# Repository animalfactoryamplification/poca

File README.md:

# PocaFamily

The Poca family of open-source synthesizers are a joint effort between Animal Factory Amplification and Synthfarm run by Varun Desai. The Poca family helps to introduce soldering techniques and the joy of synthesis using a simple set of modules.
<br>
Clone this repository to get access to the Gerber, EAGLE, and laser cutting files.

## PocaSynth

Based off the Forest Mimm's Stepped Tone Generator circuit, this bastardized Atari Punk console project is the perfect little beginner's synth for any enthusiast to build.

## PocaSeek

Building off the success of the PocaSynth, the PocaSeq is its new best friend. It's a simple 5 step sequencer, built off the CD4017 decade counter and 555 timer chip the Seq adds sequencing functionality to any willing module.

## PocaFilter

Inspired from the MFOS Noise Toaster and designed but Electroidiot, the PocaFilter brings much needed low-pass filtration to tame the gnarly square waves of the PocaSynth.

## PocaLFO

The only digital entry to the Poca lineup, the PocaLFO introduces 4 digital waveforms to modulate CV destinations of its Poca counterparts. Based on an Arduino Nano, the PocaLFO aims to educate students on how to write code for microcontrollers.

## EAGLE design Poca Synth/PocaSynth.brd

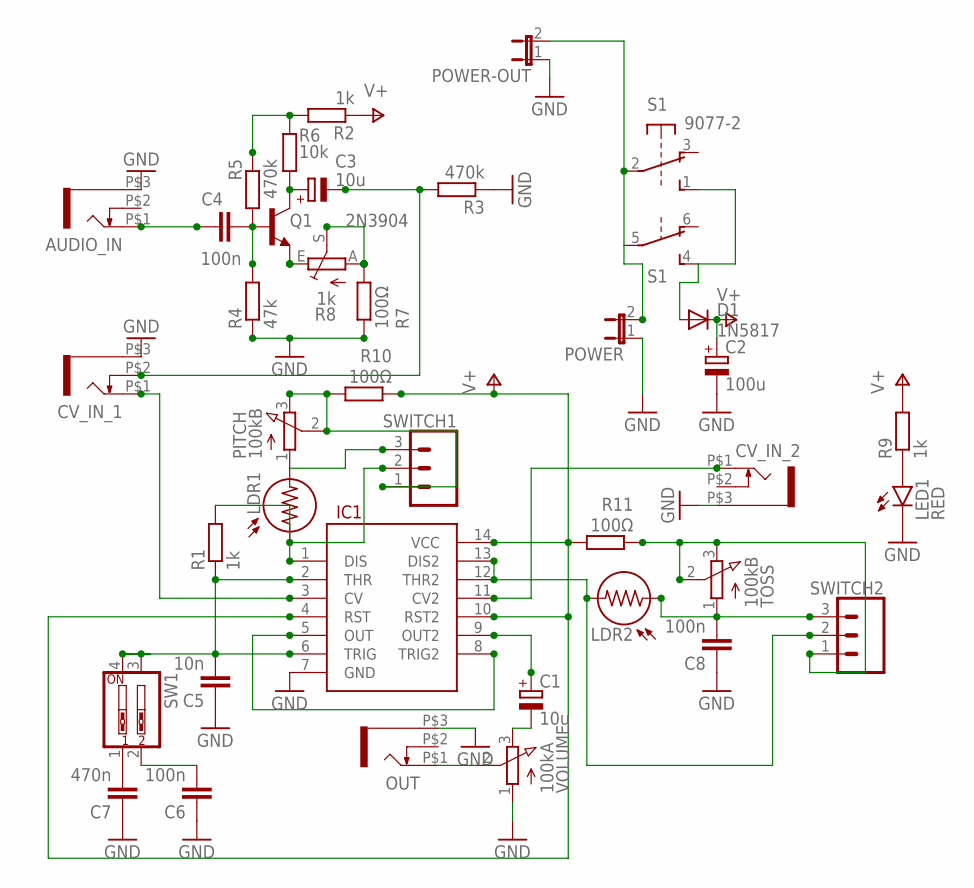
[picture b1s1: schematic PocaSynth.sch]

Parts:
AUDIO_IN: WQP-PJ301M-12_JACK
C1, C3: 10u; E2,5-7
C2: 100u; E2,5-7
C4: 100n; C050-035X075
C5: 10n; C050-030X075
C6, C8: 100n; C050-030X075
C7: 470n; C050-035X075
CV_IN_1, CV_IN_2: WQP-PJ301M-12_JACK
D1: 1N5817; DO41-10
IC1: 556; DIL14
LDR1, LDR2: LDR5MM; LDR338-54C
LED1: RED; LED3MM
OUT: WQP-PJ301M-12_JACK
PITCH: 100kB; EVUFXM
POWER: JP1E; JP1
POWER-OUT: JP1E; JP1
Q1: 2N3904; TO92-
R1, R2, R9: 1k; 0207/10
R3, R5: 470k; 0207/10
R4: 47k; 0207/10
R6: 10k; 0207/10
R7, R10, R11: 100Ω; 0207/10
R8: 1k; CA6V
S1: 9077-2
SW1: SW_DIP-2; EDG-02
SWITCH1, SWITCH2: CONN_03LOCK; 1X03_LOCK
TOSS: 100kB; EVUFXM
VOLUME: 100kA; EVUFXM

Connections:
GND: AUDIO_IN.P$3 (1), C2.-, C5.1, C6.1, C7.1, C8.1, CV_IN_1.P$3 (1), CV_IN_2.P$3 (1), IC1.7 (GND), LED1.K (C), OUT.P$3 (1), POWER.1, POWER-OUT.1, R3.1, R4.1, R7.1, VOLUME.1 (A)
unnamed: C5.2, IC1.2 (THR), IC1.6 (TRIG), R1.1, SW1.3, SW1.4
unnamed: IC1.1 (DIS), LDR1.1, R1.2, SWITCH1.2
unnamed: C6.2, SW1.2
unnamed: IC1.5 (OUT), IC1.8 (TRIG2)
unnamed: IC1.12 (THR2), IC1.13 (DIS2), LDR2.2, SWITCH2.2
unnamed: OUT.P$1 (2), VOLUME.2 (S)
unnamed: POWER.2, POWER-OUT.2, S1.2, S1.5
unnamed: CV_IN_1.P$1 (2), IC1.3 (CV)
unnamed: AUDIO_IN.P$1 (2), C4.1
unnamed: C1.+, IC1.9 (OUT2)
unnamed: C1.-, VOLUME.3 (E)
unnamed: C7.2, SW1.1
unnamed: C4.2, Q1.2 (B), R4.2, R5.1
unnamed: C3.+, Q1.1 (C), R6.1
unnamed: Q1.3 (E), R8.E
unnamed: PITCH.2 (S), PITCH.3 (E), R10.2, SWITCH1.1
unnamed: R7.2, R8.A, R8.S
unnamed: C3.-, CV_IN_1.P$2 (3), R3.2
unnamed: CV_IN_2.P$1 (2), IC1.11 (CV2)
unnamed: R11.1, SWITCH2.1, TOSS.2 (S), TOSS.3 (E)
unnamed: LDR1.2, PITCH.1 (A), SWITCH1.3
unnamed: C8.2, LDR2.1, SWITCH2.3, TOSS.1 (A)
unnamed: R2.2, R5.2, R6.2
unnamed: LED1.A, R9.1
unnamed: D1.A, S1.1 (S), S1.4 (S)
V+: C2.+, D1.C, IC1.4 (RST), IC1.10 (RST2), IC1.14 (VCC), R2.1, R9.2, R10.1, R11.2

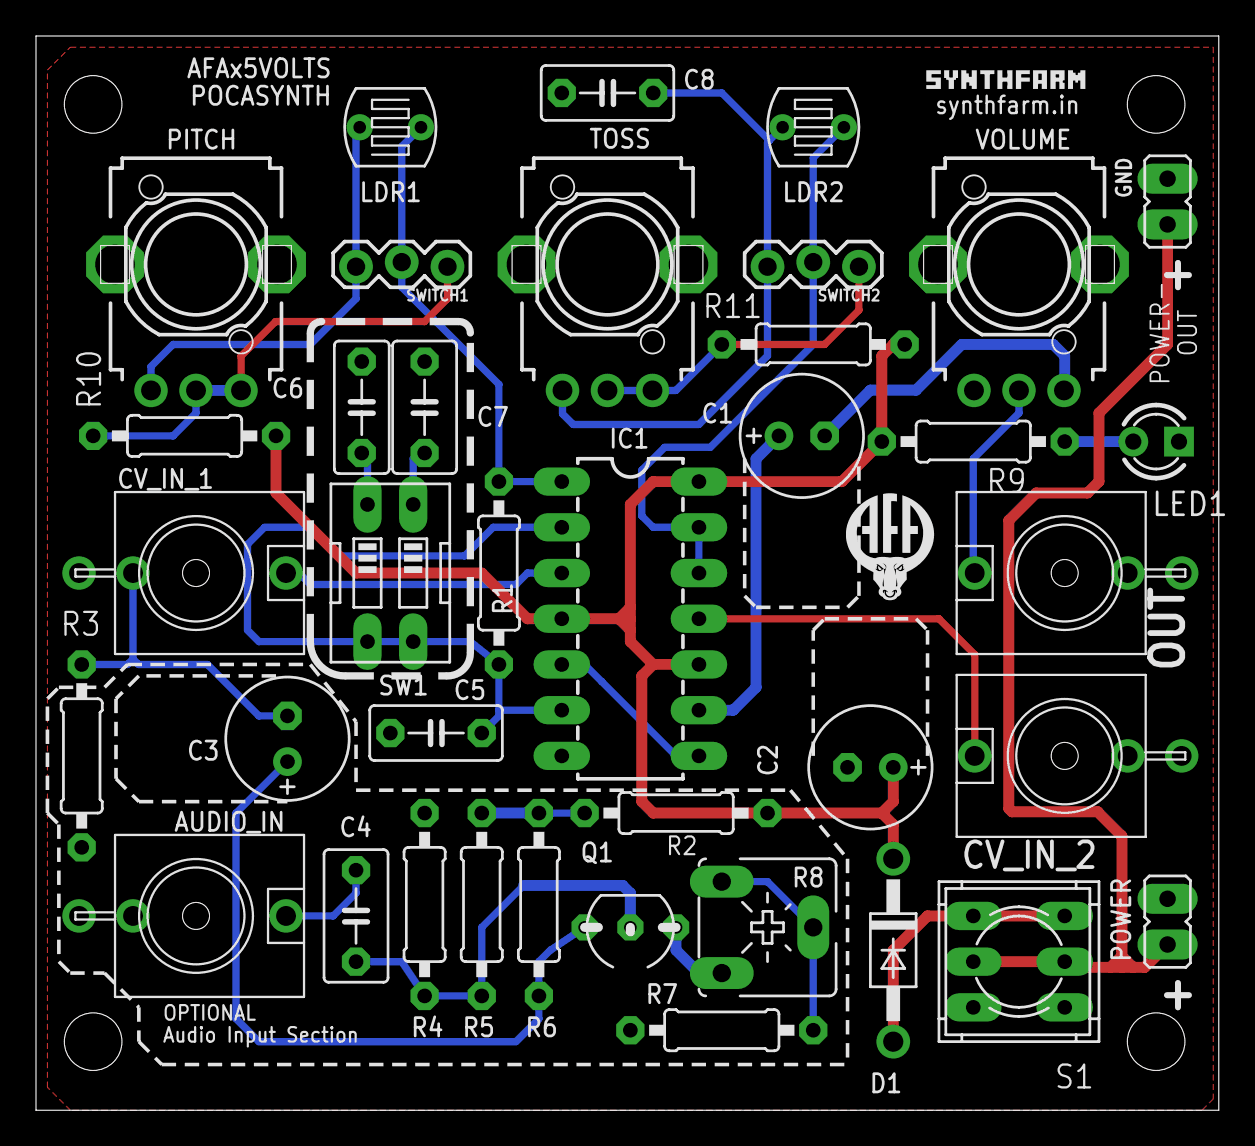
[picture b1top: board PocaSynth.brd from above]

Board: 2 copper layers, 65.7 x 59.7 mm, 38 parts (0 on the bottom side), 27 nets.

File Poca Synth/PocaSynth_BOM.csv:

"Qty";"Value";"Device";"Package";"Parts";"Description";"";
"1";"";"556";"DIL14";"IC1";"Dual timer circuit (2 555 timers in one package)";"";
"2";"";"CONN_03LOCK";"1X03_LOCK";"SWITCH1, SWITCH2";"Multi connection point. Often used as Generic Header-pin footprint for 0.1 inch spaced/style header connections";"";
"2";"";"JP1E";"JP1";"POWER, POWER-OUT";"JUMPER";"";
"2";"";"LDR5MM";"LDR338-54C";"LDR1, LDR2";"";"";
"1";"";"SW_DIP-2";"EDG-02";"SW1";"DIP SWITCH";"";
"4";"";"WQP-PJ301M-12_JACK";"WQP-PJ301M-12_JACK";"AUDIO_IN, CV_IN_1, CV_IN_2, OUT";"";"";
"1";"100kA";"EVUF3M";"EVUFXM";"VOLUME";"9 mm Square Rotary Potentiometers";"";
"2";"100kB";"EVUF3M";"EVUFXM";"PITCH, TOSS";"9 mm Square Rotary Potentiometers";"";
"2";"100n";"C-EU050-030X075";"C050-030X075";"C6, C8";"CAPACITOR, European symbol";"";
"1";"100n";"C-EU050-035X075";"C050-035X075";"C4";"CAPACITOR, European symbol";"";
"1";"100u";"CPOL-EUE2.5-7";"E2,5-7";"C2";"POLARIZED CAPACITOR, European symbol";"";
"3";"100Ω";"R-EU_0207/10";"0207/10";"R7, R10, R11";"RESISTOR, European symbol";"";
"1";"10k";"R-EU_0207/10";"0207/10";"R6";"RESISTOR, European symbol";"";
"1";"10n";"C-EU050-030X075";"C050-030X075";"C5";"CAPACITOR, European symbol";"";
"2";"10u";"CPOL-EUE2.5-7";"E2,5-7";"C1, C3";"POLARIZED CAPACITOR, European symbol";"";
"1";"1N5817";"1N4004";"DO41-10";"D1";"DIODE";"";
"3";"1k";"R-EU_0207/10";"0207/10";"R1, R2, R9";"RESISTOR, European symbol";"";
"1";"1k";"TRIM_EU-CA6V";"CA6V";"R8";"POTENTIOMETER";"";
"1";"2N3904";"2N3904";"TO92-";"Q1";"NPN Transistor";"";
"2";"470k";"R-EU_0207/10";"0207/10";"R3, R5";"RESISTOR, European symbol";"";
"1";"470n";"C-EU050-035X075";"C050-035X075";"C7";"CAPACITOR, European symbol";"";
"1";"47k";"R-EU_0207/10";"0207/10";"R4";"RESISTOR, European symbol";"";
"1";"9077-2";"9077-2";"9077-2";"S1";"MARQUARDT SWITCH 9077.0200";"";
"1";"RED";"LED3MM";"LED3MM";"LED1";"";"";

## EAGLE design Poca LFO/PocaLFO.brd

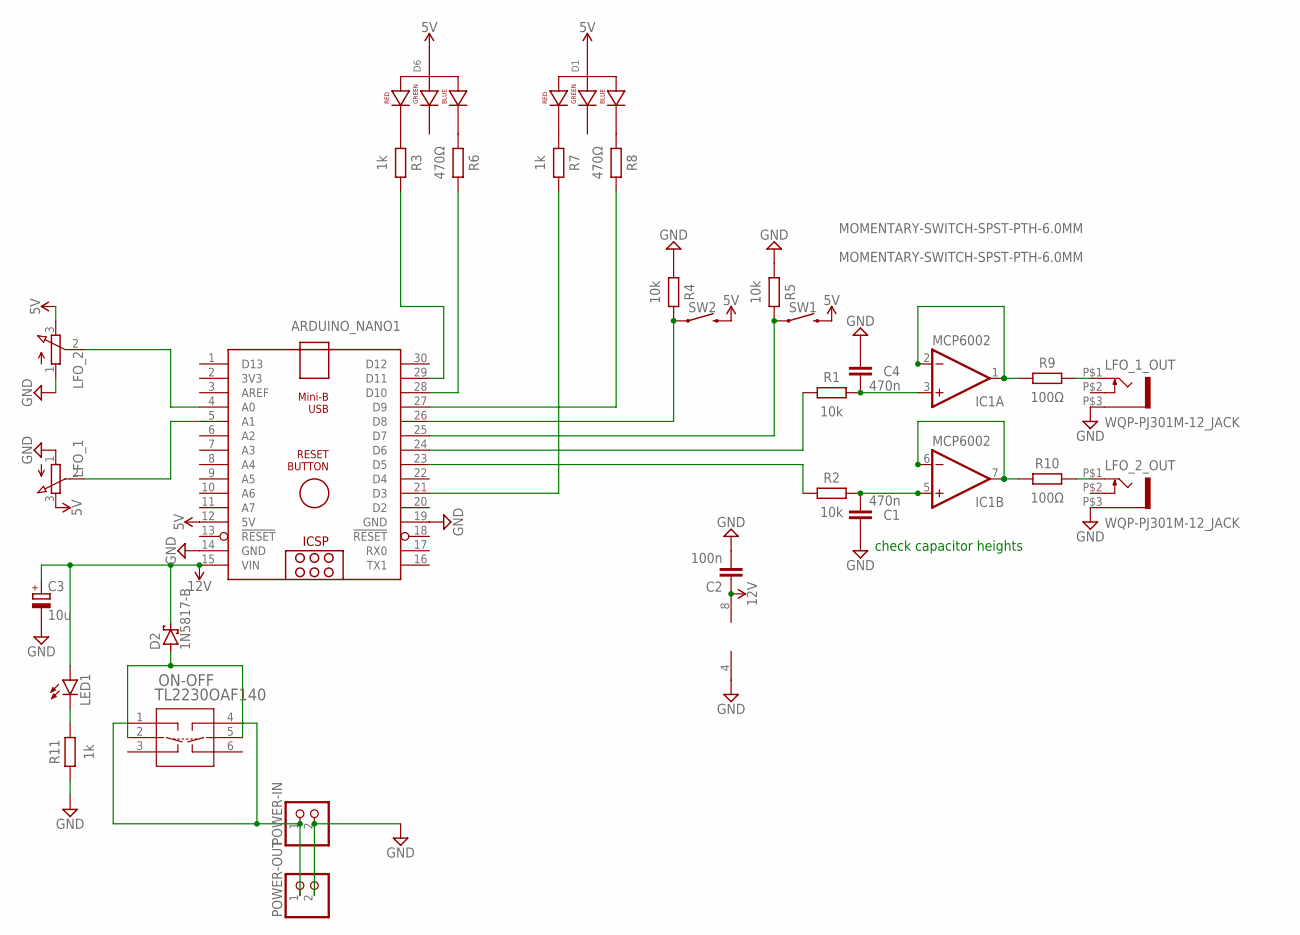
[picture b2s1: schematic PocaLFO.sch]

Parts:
ARDUINO_NANO1: ARDUINO_NANO
C1, C4: 470n; C5B3.5
C2: 100n; C2.5-4
C3: 10u; E5-5
D1, D6: LED-RGB-CA-THRUCLEAR; LED-RGB-THRU
D2: 1N5817-B; DO41-7.6
IC1: MCP6002; DIL08
LED1: LED3MM
LFO_1, LFO_2: 10kb; EVUFXM
LFO_1_OUT, LFO_2_OUT: WQP-PJ301M-12_JACK
ON-OFF: TL2230OAF140; TL2230_EWI
POWER-IN: PINHD-1X2; 1X02
POWER-OUT: PINHD-1X2; 1X02
R1, R2, R4, R5: 10k; 0207/10
R3, R7, R11: 1k; 0207/10
R6, R8: 470Ω; 0207/10
R9, R10: 100Ω; 0207/10
SW1, SW2: MOMENTARY-SWITCH-SPST-PTH-6.0MM; TACTILE_SWITCH_PTH_6.0MM

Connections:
5V: ARDUINO_NANO1.12 (5V), D1.2 (ANODE), D6.2 (ANODE), LFO_1.3 (E), LFO_2.3 (E), SW1.3 (2), SW2.3 (2)
12V: ARDUINO_NANO1.15 (VIN), C2.1, C3.+, D2.C, IC1.8 (V+), LED1.A
GND: ARDUINO_NANO1.14 (GND), ARDUINO_NANO1.19 (GND), C1.2, C2.2, C3.-, C4.1, IC1.4 (V-), LFO_1.1 (A), LFO_1_OUT.P$3 (1), LFO_2.1 (A), LFO_2_OUT.P$3 (1), POWER-IN.2, POWER-OUT.2, R4.1, R5.1, R11.1
unnamed: ARDUINO_NANO1.24 (D6), R1.1
unnamed: ARDUINO_NANO1.23 (D5), R2.1
unnamed: C4.2, IC1.3 (+IN), R1.2
unnamed: IC1.1 (OUT), IC1.2 (-IN), R9.1
unnamed: ON-OFF.1, ON-OFF.4, POWER-IN.1, POWER-OUT.1
unnamed: LFO_2_OUT.P$1 (2), R10.2
unnamed: D6.1 (RED_CATHODE), R3.1
unnamed: D6.4 (BLUE_CATHODE), R6.1
unnamed: D1.1 (RED_CATHODE), R7.1
unnamed: ARDUINO_NANO1.4 (A0), LFO_2.2 (S)
unnamed: ARDUINO_NANO1.5 (A1), LFO_1.2 (S)
unnamed: D1.4 (BLUE_CATHODE), R8.1
unnamed: ARDUINO_NANO1.29 (D11), R3.2
unnamed: ARDUINO_NANO1.26 (D8), R4.2, SW2.1
unnamed: ARDUINO_NANO1.25 (D7), R5.2, SW1.1
unnamed: ARDUINO_NANO1.28 (D10), R6.2
unnamed: ARDUINO_NANO1.21 (D3), R7.2
unnamed: ARDUINO_NANO1.27 (D9), R8.2
unnamed: C1.1, IC1.5 (+IN), R2.2
unnamed: IC1.6 (-IN), IC1.7 (OUT), R10.1
unnamed: LFO_1_OUT.P$1 (2), R9.2
unnamed: LED1.K (C), R11.2
unnamed: D2.A, ON-OFF.2, ON-OFF.5

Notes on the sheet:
check capacitor heights

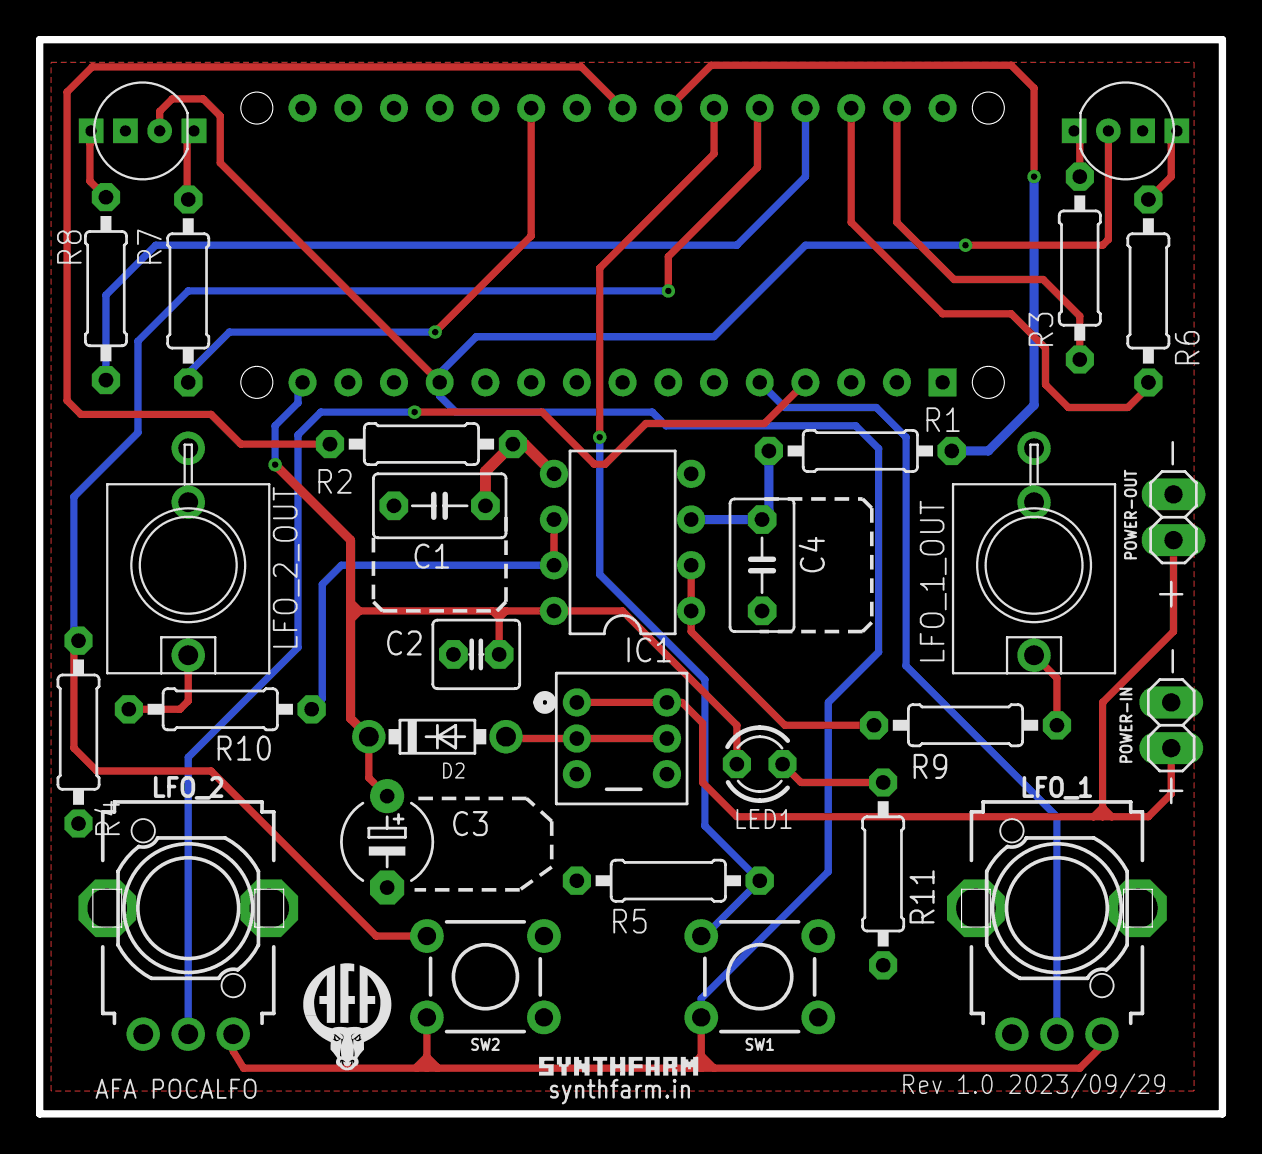
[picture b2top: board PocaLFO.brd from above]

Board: 2 copper layers, 65.7 x 59.7 mm, 30 parts (1 on the bottom side), 26 nets.

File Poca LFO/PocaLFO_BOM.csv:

"Qty";"Value";"Device";"Package";"Parts";"Description";"COPYRIGHT";"MANUFACTURER_PART_NUMBER";"MFR_NAME";"POPULARITY";"PROD_ID";"SF_SKU";"SPICEPREFIX";
"1";"";"ARDUINO_NANO";"ARDUINO_NANO";"ARDUINO_NANO1";"Arduino Nano V3.0";"";"";"";"";"";"";"";
"1";"";"LED3MM";"LED3MM";"LED1";"LED";"";"";"";"97";"";"";"";
"2";"";"PINHD-1X2";"1X02";"POWER-IN, POWER-OUT";"PIN HEADER";"";"";"";"98";"";"";"";
"1";"100n";"C2.5/4";"C2.5-4";"C2";"CAPACITOR";"";"";"";"6";"";"";"";
"2";"100Ω";"R-EU_0207/10";"0207/10";"R9, R10";"RESISTOR, European symbol";"";"";"";"81";"";"";"R";
"4";"10k";"R-EU_0207/10";"0207/10";"R1, R2, R4, R5";"RESISTOR, European symbol";"";"";"";"81";"";"";"R";
"2";"10kb";"EVUF3M";"EVUFXM";"LFO_1, LFO_2";"9 mm Square Rotary Potentiometers";"";"";"";"";"";"";"";
"1";"10u";"CPOL-EUE5-5";"E5-5";"C3";"POLARIZED CAPACITOR, European symbol";"";"";"";"6";"";"";"C";
"1";"1N5817-B";"1N5817-B";"DO41-7.6";"D2";"1.0A SCHOTTKY BARRIER RECTIFIER";"";"";"";"0";"";"";"";
"3";"1k";"R-EU_0207/10";"0207/10";"R3, R7, R11";"RESISTOR, European symbol";"";"";"";"81";"";"";"R";
"2";"470n";"C5/3.5";"C5B3.5";"C1, C4";"CAPACITOR";"";"";"";"3";"";"";"";
"2";"470Ω";"R-EU_0207/10";"0207/10";"R6, R8";"RESISTOR, European symbol";"";"";"";"81";"";"";"R";
"2";"LED-RGB-CA-THRUCLEAR";"LED-RGB-CA-THRUCLEAR";"LED-RGB-THRU";"D1, D6";"RGB Through-hole common anode";"";"";"";"";"DIO-10631";"";"";
"1";"MCP6002";"TL072P";"DIL08";"IC1";"OP AMP";"";"";"";"13";"";"";"";
"2";"MOMENTARY-SWITCH-SPST-PTH-6.0MM";"MOMENTARY-SWITCH-SPST-PTH-6.0MM";"TACTILE_SWITCH_PTH_6.0MM";"SW1, SW2";"Momentary Switch (Pushbutton) - SPST";"";"";"";"";" SWCH-08441";"COM-00097";"";
"1";"TL2230OAF140";"TL2230OAF140";"TL2230_EWI";"ON-OFF";"";"Copyright (C) 2023 Ultra Librarian. All rights reserved.";"TL2230OAF140";"E-Switch";"";"";"";"";
"2";"WQP-PJ301M-12_JACK";"WQP-PJ301M-12_JACK";"WQP-PJ301M-12_JACK";"LFO_1_OUT, LFO_2_OUT";"";"";"";"";"";"";"";"";

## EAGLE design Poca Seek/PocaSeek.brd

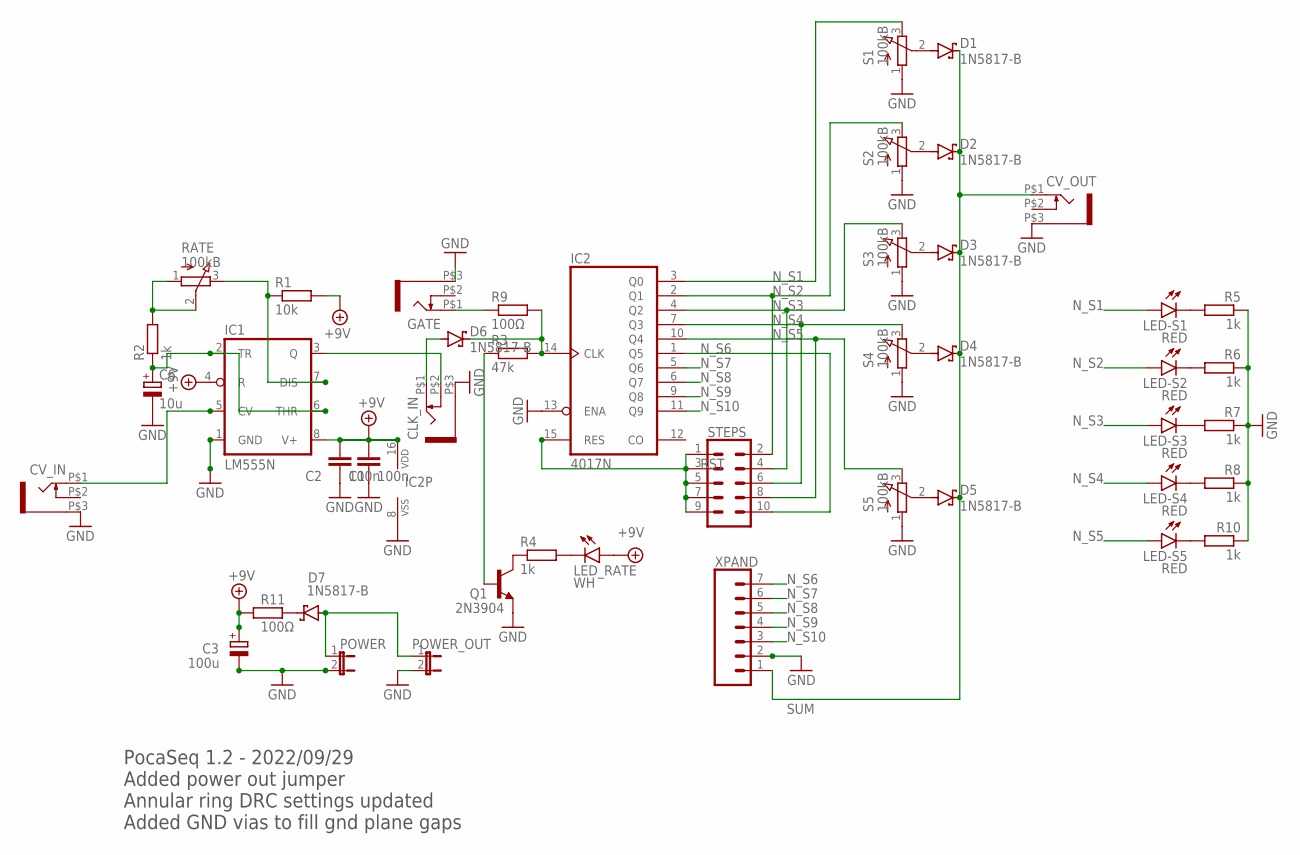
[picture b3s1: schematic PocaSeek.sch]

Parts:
C1, C2: 100n; C050-024X044
C3: 100u; E2,5-7
C6: 10u; E2,5-6
CLK_IN: WQP-PJ301M-12_JACK
CV_IN: WQP-PJ301M-12_JACK
CV_OUT: WQP-PJ301M-12_JACK
D1, D2, D3, D4, D5, D6, D7: 1N5817-B; DO41-7.6
GATE: WQP-PJ301M-12_JACK
IC1: LM555N; DIL08
IC2: 4017N; DIL16
LED-S1, LED-S2, LED-S3, LED-S4, LED-S5: RED; LED3MM
LED_RATE: WH; LED3MM
POWER: JP1E; JP1
POWER_OUT: JP1E; JP1
Q1: 2N3904; TO92
R1: 10k; 0204/7
R2, R4: 1k; 0204/7
R3: 47k; 0204/7
R5, R6, R7, R8, R10: 1k; 0204V
R9, R11: 100Ω; 0204/7
RATE: 100kB; EVUFXM
S1, S2, S3, S4, S5: 100kB; EVUFXM
STEPS: CONN_05X2PTH; 2X5
XPAND: CONN_07LOCK; 1X07_LOCK

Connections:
+9V: C1.1, C2.1, C3.+, IC1.4 (R), IC1.8 (V+), IC2.16 (VDD), LED_RATE.A, R1.2, R11.1
GND: C1.2, C2.2, C3.-, C6.-, CLK_IN.P$3 (1), CV_IN.P$3 (1), CV_OUT.P$3 (1), GATE.P$3 (1), IC1.1 (GND), IC2.8 (VSS), IC2.13 (ENA), POWER.2, POWER_OUT.2, Q1.3 (E), R5.1, R6.1, R7.1, R8.1, R10.1, S1.1 (A), S2.1 (A), S3.1 (A), S4.1 (A), S5.1 (A), XPAND.2
unnamed: D1.A, S1.2 (S)
unnamed: CLK_IN.P$2 (3), IC1.3 (Q)
unnamed: D2.A, S2.2 (S)
unnamed: D6.C, IC2.14 (CLK), R3.2, R9.2
unnamed: D5.A, S5.2 (S)
unnamed: LED-S1.K (C), R5.2
unnamed: GATE.P$1 (2), R9.1
unnamed: D3.A, S3.2 (S)
unnamed: D4.A, S4.2 (S)
unnamed: R2.2, RATE.1 (A), RATE.2 (S)
unnamed: LED-S3.K (C), R7.2
unnamed: Q1.2 (B), R3.1
unnamed: CLK_IN.P$1 (2), D6.A
unnamed: CV_IN.P$1 (2), IC1.5 (CV)
unnamed: C6.+, IC1.2 (TR), IC1.6 (THR), R2.1
unnamed: IC1.7 (DIS), R1.1, RATE.3 (E)
unnamed: LED-S4.K (C), R8.2
unnamed: Q1.1 (C), R4.1
unnamed: LED_RATE.K (C), R4.2
unnamed: LED-S5.K (C), R10.2
unnamed: LED-S2.K (C), R6.2
unnamed: D7.C, R11.2
unnamed: D7.A, POWER.1, POWER_OUT.1
N_S1: IC2.3 (Q0), LED-S1.A, S1.3 (E)
N_S2: IC2.2 (Q1), LED-S2.A, S2.3 (E), STEPS.2
N_S3: IC2.4 (Q2), LED-S3.A, S3.3 (E), STEPS.4
N_S4: IC2.7 (Q3), LED-S4.A, S4.3 (E), STEPS.6
N_S5: IC2.10 (Q4), LED-S5.A, S5.3 (E), STEPS.8
N_S6: IC2.1 (Q5), STEPS.10, XPAND.7
N_S7: IC2.5 (Q6), XPAND.6
N_S8: IC2.6 (Q7), XPAND.5
N_S9: IC2.9 (Q8), XPAND.4
N_S10: IC2.11 (Q9), XPAND.3
RST: IC2.15 (RES), STEPS.1, STEPS.3, STEPS.5, STEPS.7, STEPS.9
SUM: CV_OUT.P$1 (2), D1.C, D2.C, D3.C, D4.C, D5.C, XPAND.1

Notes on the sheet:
PocaSeq 1.2 - 2022/09/29 Added power out jumper Annular ring DRC settings updated Added GND vias to fill gnd plane gaps

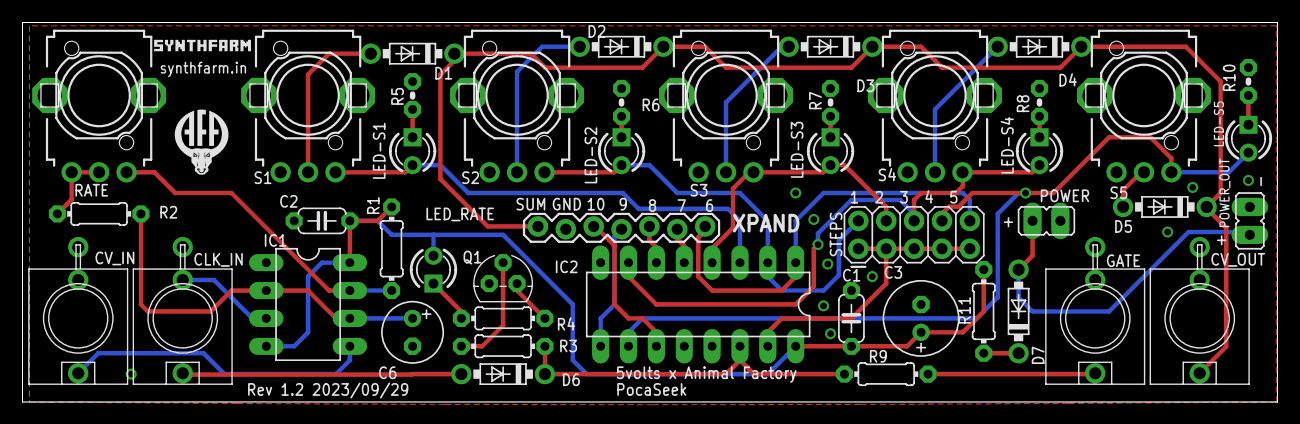
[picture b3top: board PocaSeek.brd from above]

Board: 2 copper layers, 114.4 x 34.6 mm, 45 parts (0 on the bottom side), 37 nets.

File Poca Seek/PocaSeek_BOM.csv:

"Qty";"Value";"Device";"Package";"Parts";"Description";"POPULARITY";"PROD_ID";"SF_ID";
"1";"";"CONN_05X2PTH";"2X5";"STEPS";"Multi connection point. Often used as Generic Header-pin footprint for 0.1 inch spaced/style header connections";"";"CONN-08499";"PRT-0778";
"1";"";"CONN_07LOCK";"1X07_LOCK";"XPAND";"Multi connection point. Often used as Generic Header-pin footprint for 0.1 inch spaced/style header connections";"";"";"";
"2";"";"JP1E";"JP1";"POWER, POWER_OUT";"JUMPER";"";"";"";
"4";"";"WQP-PJ301M-12_JACK";"WQP-PJ301M-12_JACK";"CLK_IN, CV_IN, CV_OUT, GATE";"";"";"";"";
"6";"100kB";"EVUF3M";"EVUFXM";"RATE, S1, S2, S3, S4, S5";"9 mm Square Rotary Potentiometers";"";"";"";
"2";"100n";"C-EU050-024X044";"C050-024X044";"C1, C2";"CAPACITOR, European symbol";"";"";"";
"1";"100u";"CPOL-EUE2.5-7";"E2,5-7";"C3";"POLARIZED CAPACITOR, European symbol";"";"";"";
"2";"100Ω";"R-EU_0204/7";"0204/7";"R9, R11";"RESISTOR, European symbol";"";"";"";
"1";"10k";"R-EU_0204/7";"0204/7";"R1";"RESISTOR, European symbol";"";"";"";
"1";"10u";"CPOL-EUE2.5-6";"E2,5-6";"C6";"POLARIZED CAPACITOR, European symbol";"";"";"";
"7";"1N5817-B";"1N5817-B";"DO41-7.6";"D1, D2, D3, D4, D5, D6, D7";"1.0A SCHOTTKY BARRIER RECTIFIER";"0";"";"";
"5";"1k";"R-EU_0204/2V";"0204V";"R5, R6, R7, R8, R10";"RESISTOR, European symbol";"";"";"";
"2";"1k";"R-EU_0204/7";"0204/7";"R2, R4";"RESISTOR, European symbol";"";"";"";
"1";"2N3904";"2N3904";"TO92";"Q1";"NPN TRANSISTOR";"";"";"";
"1";"4017N";"4017N";"DIL16";"IC2";"COUNTER/DIVIDER";"";"";"";
"1";"47k";"R-EU_0204/7";"0204/7";"R3";"RESISTOR, European symbol";"";"";"";
"1";"LM555N";"LM555N";"DIL08";"IC1";"TIMER";"";"";"";
"5";"RED";"LED3MM";"LED3MM";"LED-S1, LED-S2, LED-S3, LED-S4, LED-S5";"";"";"";"";
"1";"WH";"LED3MM";"LED3MM";"LED_RATE";"";"";"";"";

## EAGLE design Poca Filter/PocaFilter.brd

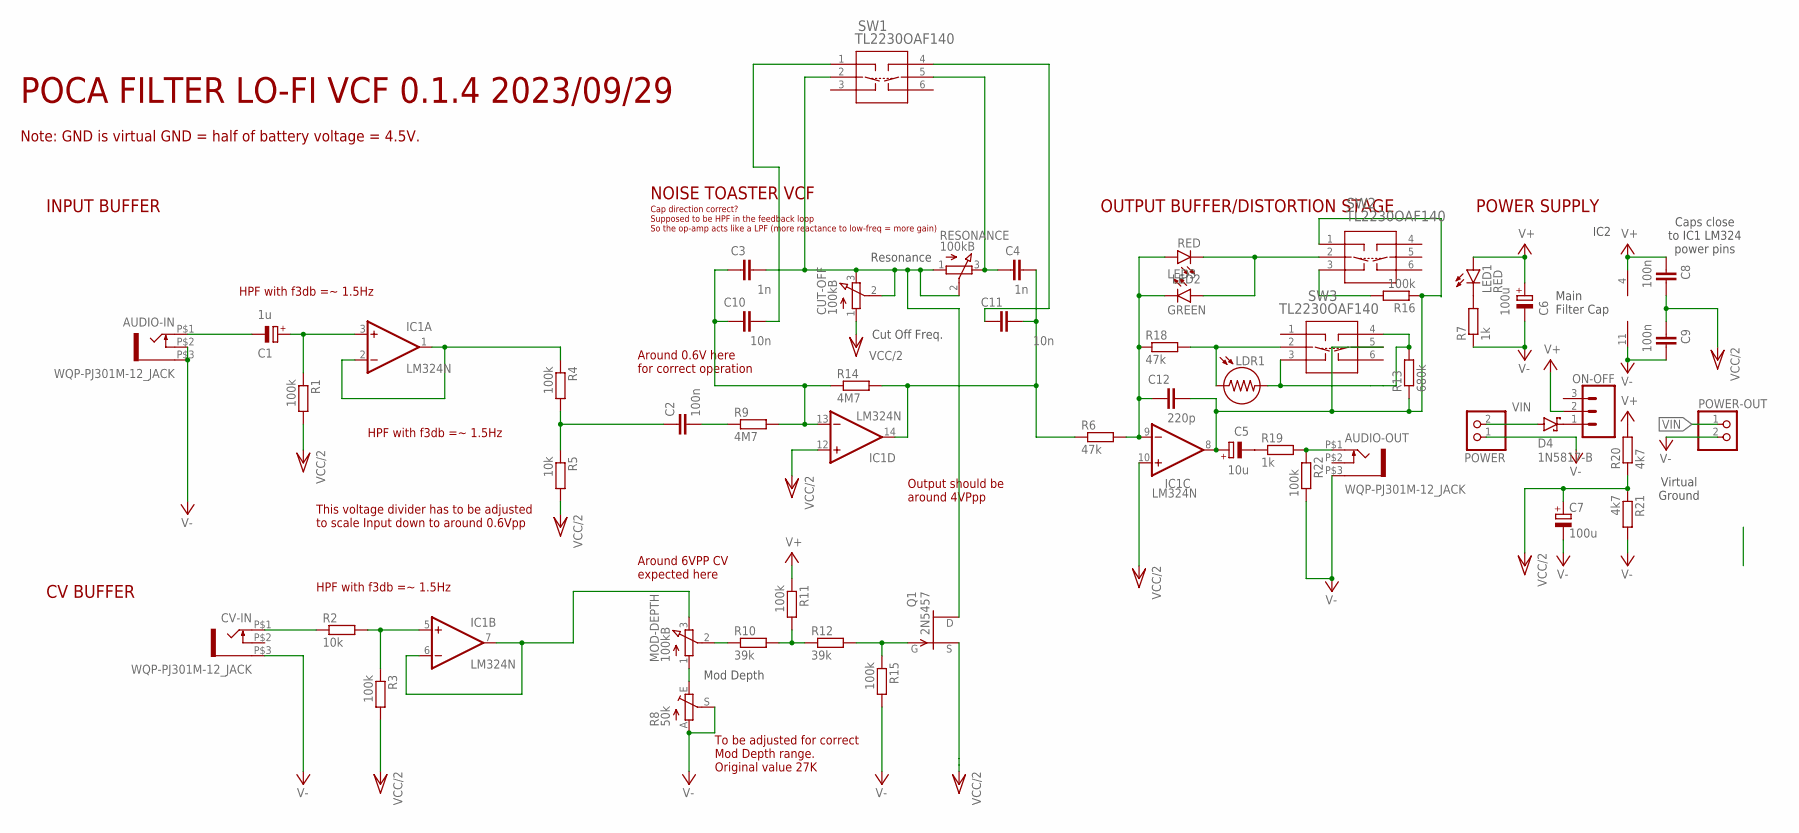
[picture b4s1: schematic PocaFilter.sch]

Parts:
AUDIO-IN: WQP-PJ301M-12_JACK
AUDIO-OUT: WQP-PJ301M-12_JACK
C1: 1u; E2,5-6
C2: 100n; C050-030X075
C3, C4: 1n; C050-030X075
C5: 10u; E2,5-6
C6: 100u; E2,5-6
C7: 100u; E2,5-6E
C8, C9: 100n; C025-025X050
C10, C11: 10n; C050-030X075
C12: 220p; C025-025X050
CUT-OFF: 100kB; EVUFXM
CV-IN: WQP-PJ301M-12_JACK
D4: 1N5817-B; DO41-7.6
IC1: LM324N; DIL14
LDR1: LDR5MM; LDR338-54C
LED1: RED; LED3MM
LED2: RED; LED_3MM
LED3: GREEN; LED_3MM
MOD-DEPTH: 100kB; EVUFXM
ON-OFF: CONN_03LOCK; 1X03_LOCK
POWER: PINHD-1X2; 1X02
POWER-OUT: PINHD-1X2; 1X02
Q1: 2N5457; TO92
R1, R3, R4, R11, R15, R22: 100k; 0207/10
R2, R5: 10k; 0207/10
R6, R18: 47k; 0207/10
R7, R19: 1k; 0207/10
R8: 50k; CA6V
R9, R14: 4M7; 0207/10
R10, R12: 39k; 0207/10
R13: 680k; 0207/10
R16: 100k; 0204/7
R20, R21: 4k7; 0207/10
RESONANCE: 100kB; EVUFXM
SW1, SW2, SW3: TL2230OAF140; TL2230_EWI

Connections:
unnamed: CV-IN.P$1 (2), R2.1
unnamed: MOD-DEPTH.1 (A), R8.E
unnamed: IC1.1 (OUT), IC1.2 (-IN), R4.1
unnamed: C1.+, IC1.3 (+IN), R1.1
unnamed: IC1.6 (-IN), IC1.7 (OUT), MOD-DEPTH.3 (E)
unnamed: AUDIO-IN.P$1 (2), C1.-
unnamed: LDR1.2, R13.2, SW3.3, SW3.4
unnamed: AUDIO-OUT.P$1 (2), R19.2, R22.1
unnamed: C5.-, R19.1
unnamed: IC1.5 (+IN), R2.2, R3.1
unnamed: C12.1, IC1.9 (-IN), LED2.A, LED3.K (C), R6.2, R18.1
unnamed: LDR1.1, R18.2, SW3.2
unnamed: LED2.K (C), LED3.A, SW2.2
unnamed: C11.1, SW1.4
unnamed: C10.2, SW1.1
unnamed: LED1.K (C), R7.2
unnamed: C5.+, C12.2, IC1.8 (OUT), R13.1, R16.1, SW2.1, SW3.5
unnamed: R16.2, SW2.3
unnamed: D4.C, ON-OFF.1
unnamed: C2.2, R9.1
unnamed: C3.1, C10.1, IC1.13 (-IN), R9.2, R14.1
unnamed: R10.2, R11.2, R12.1
unnamed: Q1.1 (G), R12.2, R15.1
V+: C6.+, C8.1, IC1.4 (V+), LED1.A, ON-OFF.2, R11.1, R20.2
V-: AUDIO-IN.P$2 (3), AUDIO-IN.P$3 (1), AUDIO-OUT.P$3 (1), C6.-, C7.-, C9.2, CV-IN.P$3 (1), IC1.11 (V-), POWER.1, POWER-OUT.2, R7.1, R8.A, R8.S, R15.2, R21.2, R22.2
VCC/2: C7.+, C8.2, C9.1, CUT-OFF.1 (A), IC1.10 (+IN), IC1.12 (+IN), Q1.2 (S), R1.2, R3.2, R5.2, R20.1, R21.1
VIN: D4.A, POWER.2, POWER-OUT.1
X8: C2.1, R4.2, R5.1
X9: C3.2, CUT-OFF.2 (S), CUT-OFF.3 (E), Q1.3 (D), RESONANCE.1 (A), RESONANCE.2 (S), SW1.2
X10: C4.1, RESONANCE.3 (E), SW1.5
X12: C4.2, C11.2, IC1.14 (OUT), R6.1, R14.2
X14: MOD-DEPTH.2 (S), R10.1

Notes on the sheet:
Mod Depth
NOISE TOASTER VCF
Cut Off Freq.
Resonance
POWER SUPPLY
IC2
Virtual Ground
Caps close to IC1 LM324 power pins
Main Filter Cap
POCA FILTER LO-FI VCF 0.1.4 2023/09/29
This voltage divider has to be adjusted to scale Input down to around 0.6Vpp
OUTPUT BUFFER/DISTORTION STAGE
INPUT BUFFER
CV BUFFER
Around 6VPP CV expected here
To be adjusted for correct Mod Depth range. Original value 27K
Note: GND is virtual GND = half of battery voltage = 4.5V.
Output should be around 4VPpp
Around 0.6V here for correct operation
HPF with f3db =~ 1.5Hz
Cap direction correct? Supposed to be HPF in the feedback loop So the op-amp acts like a LPF (more reactance to low-freq = more gain)

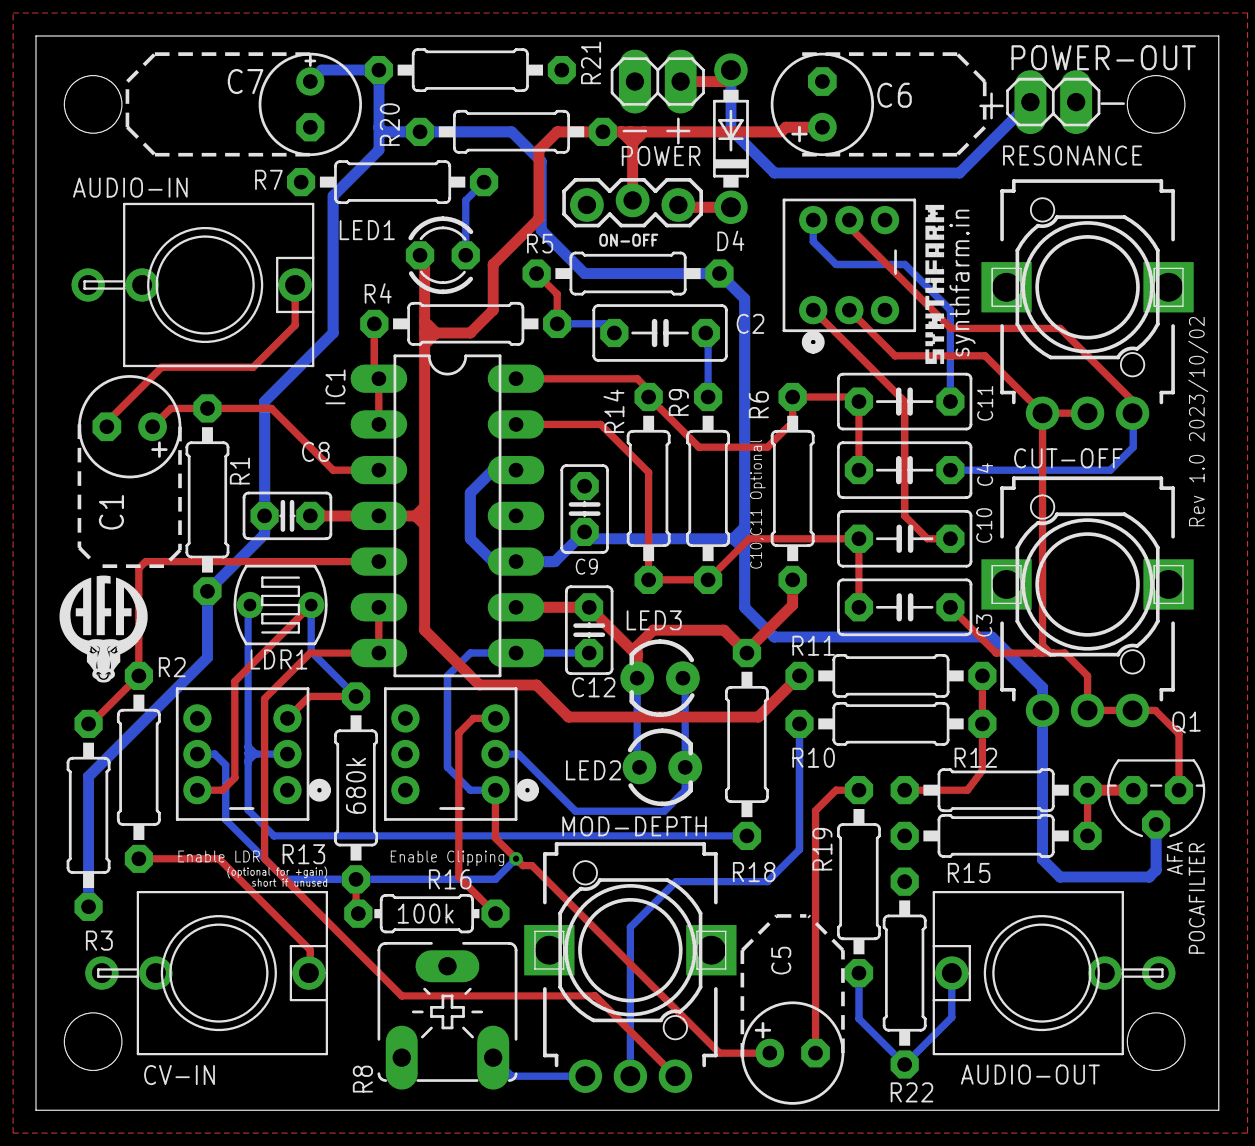
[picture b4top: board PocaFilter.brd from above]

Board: 2 copper layers, 65.7 x 59.7 mm, 52 parts (0 on the bottom side), 32 nets.

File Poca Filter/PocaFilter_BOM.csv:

"Qty";"Value";"Device";"Package";"Parts";"Description";"COPYRIGHT";"MANUFACTURER_PART_NUMBER";"MFR_NAME";"POPULARITY";"PROD_ID";"SPICEPREFIX";
"1";"";"CONN_03LOCK";"1X03_LOCK";"ON-OFF";"Multi connection point. Often used as Generic Header-pin footprint for 0.1 inch spaced/style header connections";"";"";"";"";"";"";
"1";"";"LDR5MM";"LDR338-54C";"LDR1";"";"";"";"";"";"";"";
"2";"";"PINHD-1X2";"1X02";"POWER, POWER-OUT";"PIN HEADER";"";"";"";"98";"";"";
"1";"100k";"R-EU_0204/7";"0204/7";"R16";"RESISTOR, European symbol";"";"";"";"79";"";"R";
"6";"100k";"R-EU_0207/10";"0207/10";"R1, R3, R4, R11, R15, R22";"RESISTOR, European symbol";"";"";"";"81";"";"R";
"3";"100kB";"EVUF3M";"EVUFXM";"CUT-OFF, MOD-DEPTH, RESONANCE";"9 mm Square Rotary Potentiometers";"";"";"";"0";"";"";
"2";"100n";"C-EU025-025X050";"C025-025X050";"C8, C9";"CAPACITOR, European symbol";"";"";"";"65";"";"C";
"1";"100n";"C-EU050-030X075";"C050-030X075";"C2";"CAPACITOR, European symbol";"";"";"";"9";"";"C";
"1";"100u";"CPOL-EUE2,5-6E";"E2,5-6E";"C7";"POLARIZED CAPACITOR, European symbol";"";"";"";"27";"";"C";
"1";"100u";"CPOL-EUE2.5-6";"E2,5-6";"C6";"POLARIZED CAPACITOR, European symbol";"";"";"";"26";"";"C";
"2";"10k";"R-EU_0207/10";"0207/10";"R2, R5";"RESISTOR, European symbol";"";"";"";"81";"";"R";
"2";"10n";"C-EU050-030X075";"C050-030X075";"C10, C11";"CAPACITOR, European symbol";"";"";"";"9";"";"C";
"1";"10u";"CPOL-EUE2.5-6";"E2,5-6";"C5";"POLARIZED CAPACITOR, European symbol";"";"";"";"26";"";"C";
"1";"1N5817-B";"1N5817-B";"DO41-7.6";"D4";"1.0A SCHOTTKY BARRIER RECTIFIER";"";"";"";"0";"";"";
"2";"1k";"R-EU_0207/10";"0207/10";"R7, R19";"RESISTOR, European symbol";"";"";"";"81";"";"R";
"2";"1n";"C-EU050-030X075";"C050-030X075";"C3, C4";"CAPACITOR, European symbol";"";"";"";"9";"";"C";
"1";"1u";"CPOL-EUE2.5-6";"E2,5-6";"C1";"POLARIZED CAPACITOR, European symbol";"";"";"";"26";"";"C";
"1";"220p";"C-EU025-025X050";"C025-025X050";"C12";"CAPACITOR, European symbol";"";"";"";"65";"";"C";
"1";"2N5457";"J201";"TO92";"Q1";"TEMIC / Siliconix N-Channel JFET";"";"";"";"0";"";"";
"2";"39k";"R-EU_0207/10";"0207/10";"R10, R12";"RESISTOR, European symbol";"";"";"";"81";"";"R";
"2";"47k";"R-EU_0207/10";"0207/10";"R6, R18";"RESISTOR, European symbol";"";"";"";"81";"";"R";
"2";"4M7";"R-EU_0207/10";"0207/10";"R9, R14";"RESISTOR, European symbol";"";"";"";"81";"";"R";
"2";"4k7";"R-EU_0207/10";"0207/10";"R20, R21";"RESISTOR, European symbol";"";"";"";"81";"";"R";
"1";"50k";"TRIM_EU-CA6V";"CA6V";"R8";"POTENTIOMETER";"";"";"";"10";"";"";
"1";"680k";"R-EU_0207/10";"0207/10";"R13";"RESISTOR, European symbol";"";"";"";"81";"";"R";
"1";"GREEN";"LED3MM";"LED_3MM";"LED3";"LED (Generic)";"";"";"";"";"DIO-08794";"";
"1";"LM324N";"LM324N";"DIL14";"IC1";"OP AMP";"";"";"";"9";"";"";
"1";"RED";"LED3MM";"LED3MM";"LED1";"LED";"";"";"";"97";"";"";
"1";"RED";"LED3MM";"LED_3MM";"LED2";"LED (Generic)";"";"";"";"";"DIO-08794";"";
"3";"TL2230OAF140";"TL2230OAF140";"TL2230_EWI";"SW1, SW2, SW3";"";"Copyright (C) 2023 Ultra Librarian. All rights reserved.";"TL2230OAF140";"E-Switch";"";"";"";
"3";"WQP-PJ301M-12_JACK";"WQP-PJ301M-12_JACK";"WQP-PJ301M-12_JACK";"AUDIO-IN, AUDIO-OUT, CV-IN";"";"";"";"";"";"";"";

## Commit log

2023-11-08 Uploaded files
2023-11-08 Added comments

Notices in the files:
parts and their libraries:
SparkFun-LED: Licensing: Creative Commons ShareAlike 4.0 International - https://creativecommons.org/licenses/by-sa/4.0
COPYRIGHT: Copyright (C) 2023 Ultra Librarian. All rights reserved.
SparkFun-AnalogIC: Licensing: CC v3.0 Share-Alike You are welcome to use this library for commercial purposes.
